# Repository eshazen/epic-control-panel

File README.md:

# epic-control-panel

Simple programmable controller for various applications in EPIC

KiCAD PCB design copied from SCOS project for BME research.

Applications:

* Wind tunnel controller for probe angle/height

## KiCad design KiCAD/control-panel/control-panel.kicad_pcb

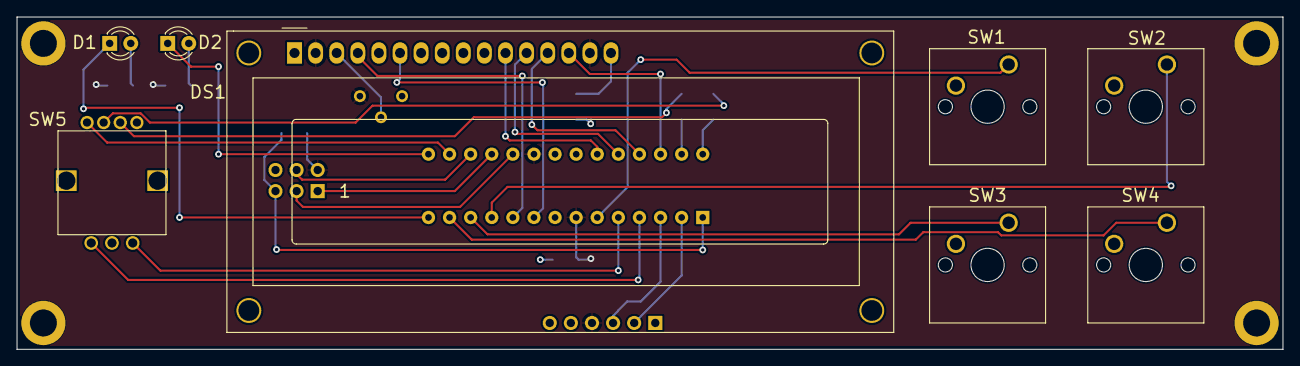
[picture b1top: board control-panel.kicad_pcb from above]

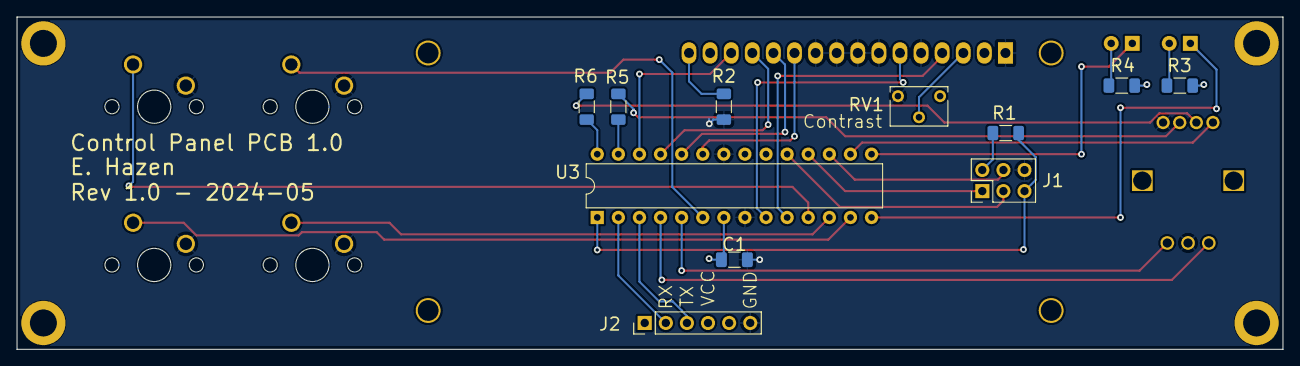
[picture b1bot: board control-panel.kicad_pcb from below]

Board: 2 copper layers, 152.4 x 40.0 mm, 23 parts (11 on the bottom side), 31 nets.

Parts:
C1: 0.1uF; C_1206_3216Metric_Pad1.33x1.80mm_HandSolder
D1, D2: LED; LED_D3.0mm
DS1: RC1602A; WC1602A
H1, H2, H3, H4: MountingHole; mtg_hole_4-40
J1: Conn_02x03_Odd_Even; PinHeader_2x03_P2.54mm_Vertical
J2: Conn_01x06; PinHeader_1x06_P2.54mm_Vertical
R1: 10k; R_1206_3216Metric_Pad1.30x1.75mm_HandSolder
R2, R3, R4, R5, R6: 470; R_1206_3216Metric_Pad1.30x1.75mm_HandSolder
RV1: 10k; Potentiometer_Bourns_3266W_Vertical
SW1, SW2, SW3, SW4: SW_Push; SW_Cherry_MX_1.00u_PCB
SW5: COM-15140; rotary-RG-3D
U3: ATmega328-P; DIP-28_W7.62mm

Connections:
/D0: DS1.11 (DB4), U3.23 (PC0)
/D1: DS1.12 (DB5), U3.24 (PC1)
/D2: DS1.13 (DB6), U3.25 (PC2)
/D3: DS1.14 (DB7), U3.26 (PC3)
/EN: DS1.6 (E), U3.9 (XTAL1/PB6)
/ENC_A: SW5.A, U3.4 (PD2)
/ENC_B: SW5.B, U3.5 (PD3)
/ENC_GRN: R6.2, U3.28 (PC5)
/ENC_RED: R5.2, U3.27 (PC4)
/ENC_SW: SW5.4 (S1), U3.16 (PB2)
/MISO: J1.1, U3.18 (PB4)
/MOSI: J1.4, U3.17 (PB3)
/RS: DS1.4 (RS), U3.10 (XTAL2/PB7)
/RXD: J2.2, U3.2 (PD0)
/SCK: J1.3, U3.19 (PB5)
/SW0: SW1.1, U3.6 (PD4)
/SW1: SW2.1, U3.11 (PD5)
/SW2: SW3.1, U3.12 (PD6)
/SW3: SW4.1, U3.13 (PD7)
/TXD: J2.3, U3.3 (PD1)
/nRST: J1.5, R1.2, U3.1 (~RESET/PC6)
GND: C1.2, DS1.1 (VSS), DS1.5 (R/W), DS1.7 (DB0), DS1.8 (DB1), DS1.9 (DB2), DS1.10 (DB3), J1.6, J2.6, R2.2, RV1.3, SW1.2, SW2.2, SW3.2, SW4.2, SW5.1 (S2), SW5.C, U3.8 (GND), U3.22 (GND)
unnamed: D1.2 (A), R3.2
unnamed: D1.1 (K), U3.14 (PB0)
unnamed: D2.2 (A), R4.2
unnamed: D2.1 (K), U3.15 (PB1)
unnamed: DS1.16 (K), R2.1
unnamed: DS1.3 (VO), RV1.2
unnamed: R6.1, SW5.3 (GREEN)
unnamed: R5.1, SW5.2 (RED)
VCC: C1.1, DS1.2 (VDD), DS1.15 (A/VEE), J1.2, J2.4, R1.1, R3.1, R4.1, RV1.1, U3.7 (VCC), U3.20 (AVCC)

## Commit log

2024-07-23 Add control panel
2024-07-25 Add front panel DXF for control panel
2024-07-25 Add step of control panel
2024-07-30 Update README with wiring
2024-07-30 initial motor control test software
2024-07-31 readme
2024-10-09 add wiring diagram
2024-10-09 final wiring diagram
2024-10-22 update wiring diagram pdf
2024-10-22 update gitignore
2024-10-22 Move stepping motor demo to own folder, restore control-panel-test
2024-10-23 starting WT framework, 1ms timer test
2024-10-23 UP/DOWN for test; working on step_int
2024-10-29 add blinky code
2024-10-30 README, working UP/DOWN test run motor
2024-10-30 full test display / keys / LEDs / motor
